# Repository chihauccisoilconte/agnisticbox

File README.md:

# agnisticbox
This repo contains all the materials needed to build an Agnostic Box

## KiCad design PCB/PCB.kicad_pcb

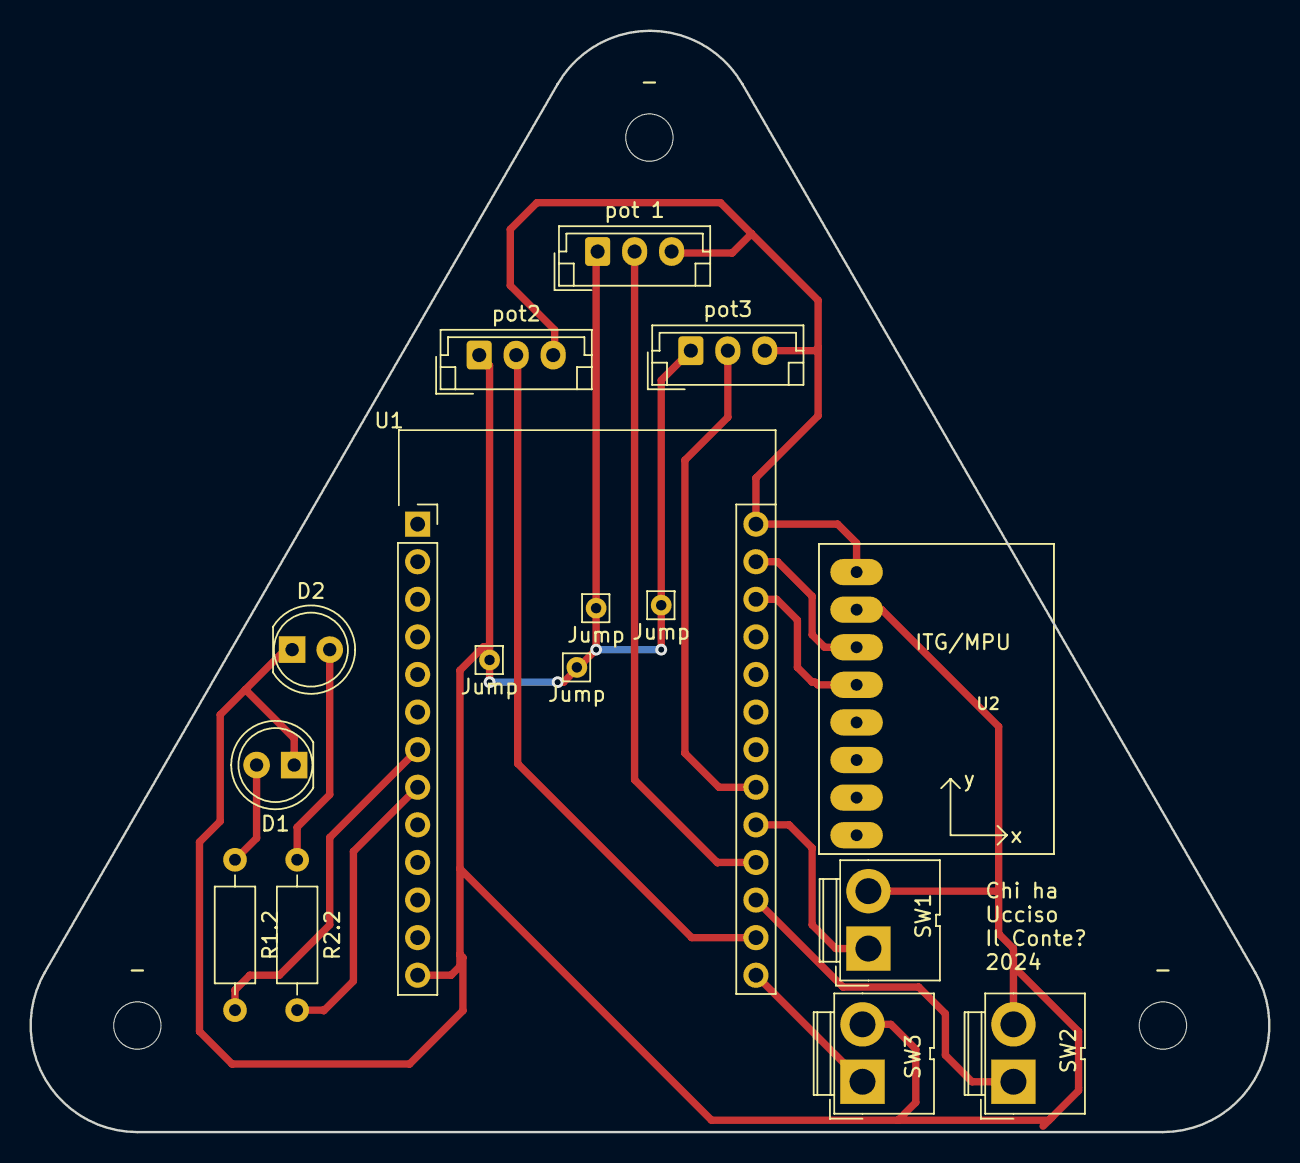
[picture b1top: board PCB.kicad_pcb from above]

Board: 2 copper layers, 83.7 x 74.4 mm, 19 parts (0 on the bottom side), 14 nets.

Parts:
-: MountingHole_3.2mm_M3_DIN965
-#2, -#3: MountingHole_3.2mm_M3_DIN965
D1, D2: LED; LED_D5.0mm
Jump: Jump; Pin_D0.7mm_L6.5mm_W1.8mm_FlatFork
Jump#2: jump; Pin_D0.7mm_L6.5mm_W1.8mm_FlatFork
Jump#3, Jump#4: Jump; Pin_D0.7mm_L6.5mm_W1.8mm_FlatFork
R1.2, R2.2: R; R_Axial_DIN0207_L6.3mm_D2.5mm_P10.16mm_Horizontal
SW1, SW2, SW3: SW_DIP_x01; JWT_A3963_1x02_P3.96mm_Vertical
U1: esp32_wemos_lolin32_lite
U2: GY-521
pot2, pot3: R_Potentiometer; JST_EH_B3B-EH-A_1x03_P2.50mm_Vertical
pot 1: R_Potentiometer; JST_EH_B3B-EH-A_1x03_P2.50mm_Vertical

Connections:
GND: D1.1 (K), D2.1 (K), SW1.2, SW2.2, SW3.2, U1.13 (GND), U2.GND, pot2.1, pot3.1, pot 1.1
unnamed: D1.2 (A), R1.2.1
unnamed: D2.2 (A), R2.2.1
unnamed: R1.2.2, U1.7 (33)
unnamed: R2.2.2, U1.8 (25)
unnamed: U1.17 (0), pot 1.2
unnamed: U1.15, pot2.2
unnamed: U1.19 (16), pot3.2
unnamed: SW1.1, U1.18 (4)
unnamed: SW2.1, U1.16 (2)
unnamed: SW3.1, U1.14 (13)
unnamed: U1.24 (19), U2.SDA
unnamed: U1.25 (22), U2.SCL
VCC: U1.26 (3v3), U2.VCC, pot2.3, pot3.3, pot 1.3
